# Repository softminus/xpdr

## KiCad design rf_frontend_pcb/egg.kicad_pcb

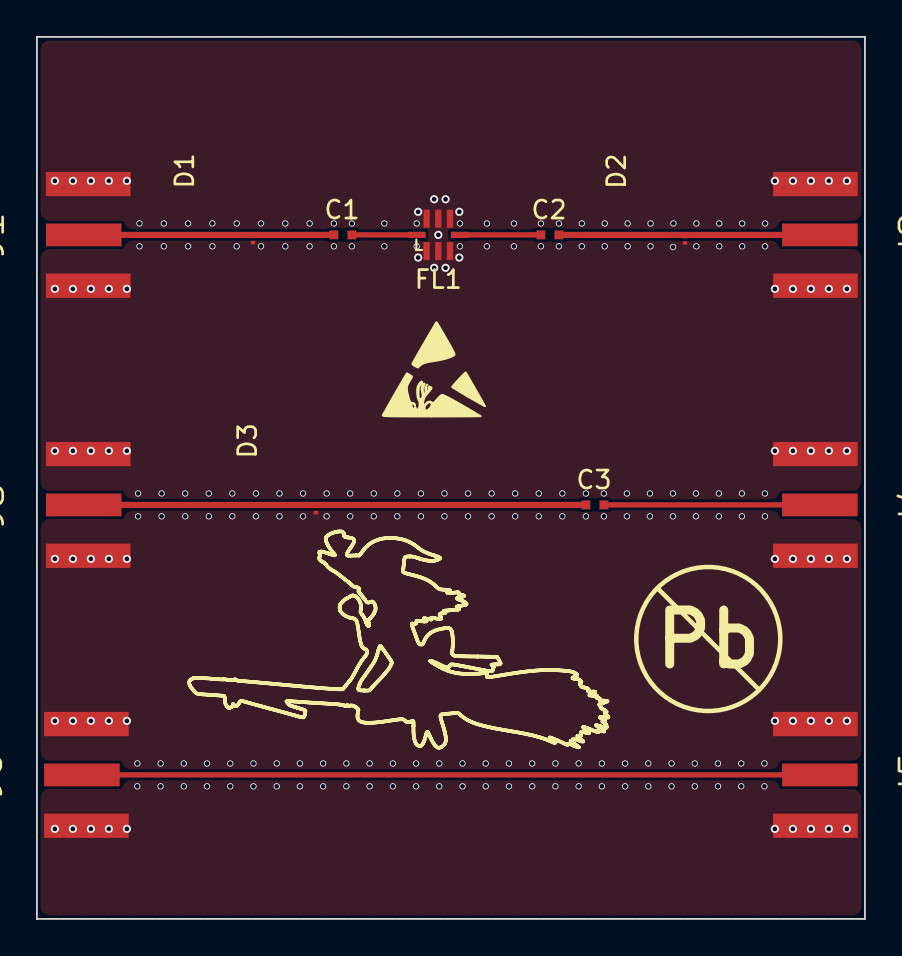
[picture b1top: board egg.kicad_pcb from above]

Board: 4 copper layers, 46.0 x 49.0 mm, 14 parts (0 on the bottom side), 8 nets.

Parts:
C1, C2, C3: C_Small; EIA_0402_CAP_NOSILK
D1, D2, D3: ESD101B102ELSE6327XTSA1_INF; ESD101B102ELSE6327XTSA1
FL1: LFCG-1200+; GE0805C-2
J1, J2, J3, J4, J5, J6: CONN_COAXIAL; CONN_SMA_EDGE_SAMTEC_SMA_J_P_H_ST_EM1
LOGO_PB_FREE_8MM: VAL**; LOGO_PB_FREE_8MM

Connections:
GND: D1.2, D2.2, D3.2, FL1.1, FL1.2, FL1.3, FL1.5, FL1.6, FL1.7, J1.2, J2.2, J3.2, J4.2, J5.2, J6.2
unnamed: C1.1, FL1.8
unnamed: C1.2, D1.1, J1.1
unnamed: C2.1, D2.1, J2.1
unnamed: C2.2, FL1.4
unnamed: C3.1, J4.1
unnamed: C3.2, D3.1, J3.1
unnamed: J5.1, J6.1

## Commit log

2018-03-24 complex_mixer.v
2018-03-25 0.5 offset
2018-03-25 force use of both components of mixer output
2018-03-25 mixer is pipelined now
2018-03-27 makefile tracks dependencies
2018-05-31 suppress errors
2018-05-31 print variables with printf
2018-06-06 retry mixer
2018-06-06 verilator testbench injects signals
2018-08-01 begin work on GMSK modulator.
2018-08-14 tb-top.cc
2018-08-14 gmsk_phasetables.py
2018-08-15 starting to look decent.
2018-08-15 graph.png
2018-08-16 reorder
2018-08-16 traj_one
2018-08-16 figured out how to open files in python
2018-08-16 master phases
2018-08-16 sine of master phases
2018-08-16 reorg code
2018-08-22 remove old files
2018-08-22 run on proper indices, (0 to 63, not 0 to 64), convert to integers for output purposes
2018-08-22 graph of all four master ROMs.
2018-08-22 2s complement :(
2018-08-23 output hex
2018-08-23 rename
2018-08-23 try reading from block ram
2018-08-23 gitignore + st3
2018-08-23 make verilator happy
2018-08-23 super basic verilator setup
2018-08-23 make testbench output gnuplottable output
    likewise, make phasetable generator output gnuplottable output
2018-08-23 added warning comment
2018-08-23 SAMPLES_PER_SYMBOL and BITS_PER_SAMPLE
2018-08-23 other master curves
2018-08-23 output non-hex of all four
2018-08-23 make fake tables to trivially see if verilog is misbehaving
2018-08-23 run sim and output into verilog_out.txt
2018-08-23 fake curves
2018-08-23 comment out irrelevant signals to avoid confusion
2018-08-23 start working on symbol strobe
2018-08-23 4 space tabs, also toggle the symbol strobe
2018-08-23 sample multiple times per clock interval, to capture combinatorial logic settling
2018-08-23 always clock a ROM lookup
2018-08-24 play around with negation
2018-09-26 rm modea
2021-02-08 upload kicad files here
